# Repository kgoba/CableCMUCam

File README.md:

Automatic motion tracking with CMUCam Pixy camera and CableCam, implemented on MBED Nucleo board.

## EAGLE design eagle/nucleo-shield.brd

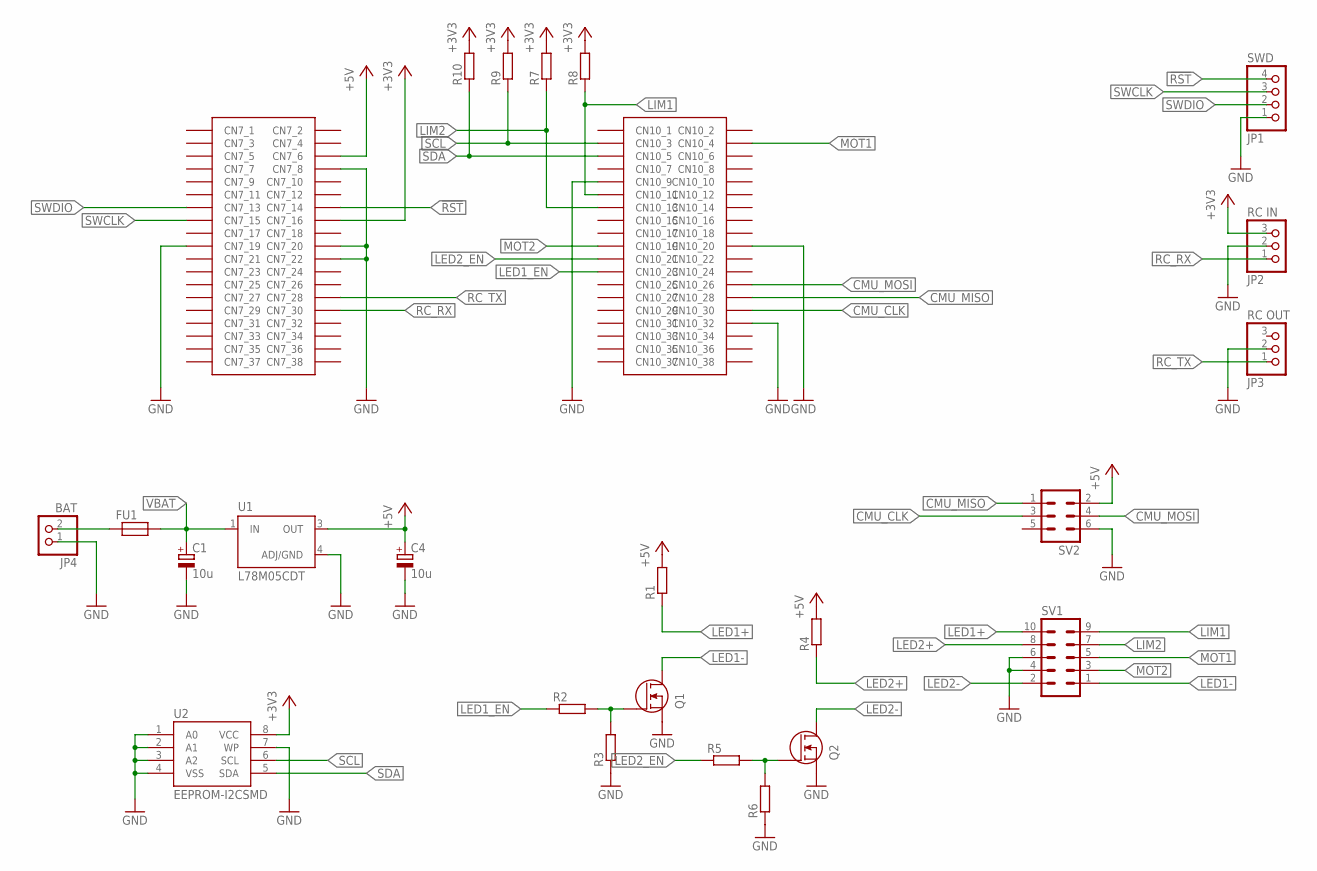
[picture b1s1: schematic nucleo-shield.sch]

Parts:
C1, C4: 10u; SMC_A
FU1: PTC_FUSE; C1812K
JP1: SWD; 1X04
JP2: RC IN; 1X03
JP3: RC OUT; 1X03
JP4: BAT; 1X02
Q1, Q2: MOSFET-N-SOT23-3; SOT23-3
R1, R2, R3, R4, R5, R6, R7, R8, R9, R10: R-EU_R0805; R0805
SV1: ML10L
SV2: ML6L
U1: L78M05CDT; DPAK
U2: EEPROM-I2CSMD; SO08
U$2: NUCLEO-MORPHO-64; NUCLEO-64-MORPHO

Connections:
!RST: JP1.4, U$2.CN7_14
+3V3: JP2.3, R7.2, R8.2, R9.2, R10.2, U2.8 (VCC), U$2.CN7_16
+5V: C4.+, R1.2, R4.2, SV2.2, U1.3 (OUT), U$2.CN7_6
CMU_CLK: SV2.3, U$2.CN10_30
CMU_MISO: SV2.1, U$2.CN10_28
CMU_MOSI: SV2.4, U$2.CN10_26
GND: C1.-, C4.-, JP1.1, JP2.2, JP3.2, JP4.1, Q1.2 (S), Q2.2 (S), R3.1, R6.1, SV1.4, SV1.6, SV2.6, U1.4 (ADJ/GND), U2.1 (A0), U2.2 (A1), U2.3 (A2), U2.4 (VSS), U2.7 (WP), U$2.CN7_8, U$2.CN7_19, U$2.CN7_20, U$2.CN7_22, U$2.CN10_9, U$2.CN10_20, U$2.CN10_32
LED1+: R1.1, SV1.10
LED1-: Q1.3 (D), SV1.1
LED1_EN: R2.1, U$2.CN10_23
LED2+: R4.1, SV1.8
LED2-: Q2.3 (D), SV1.2
LED2_EN: R5.1, U$2.CN10_21
LIM1: R8.1, SV1.9, U$2.CN10_11
LIM2: R7.1, SV1.7, U$2.CN10_13
MOT1: SV1.5, U$2.CN10_4
MOT2: SV1.3, U$2.CN10_19
unnamed: Q1.1 (G), R2.2, R3.2
unnamed: FU1.1, JP4.2
unnamed: Q2.1 (G), R5.2, R6.2
RC_RX: JP2.1, U$2.CN7_30
RC_TX: JP3.1, U$2.CN7_28
SCL: R9.1, U2.6 (SCL), U$2.CN10_3
SDA: R10.1, U2.5 (SDA), U$2.CN10_5
SWCLK: JP1.3, U$2.CN7_15
SWDIO: JP1.2, U$2.CN7_13
VBAT: C1.+, FU1.2, U1.1 (IN)

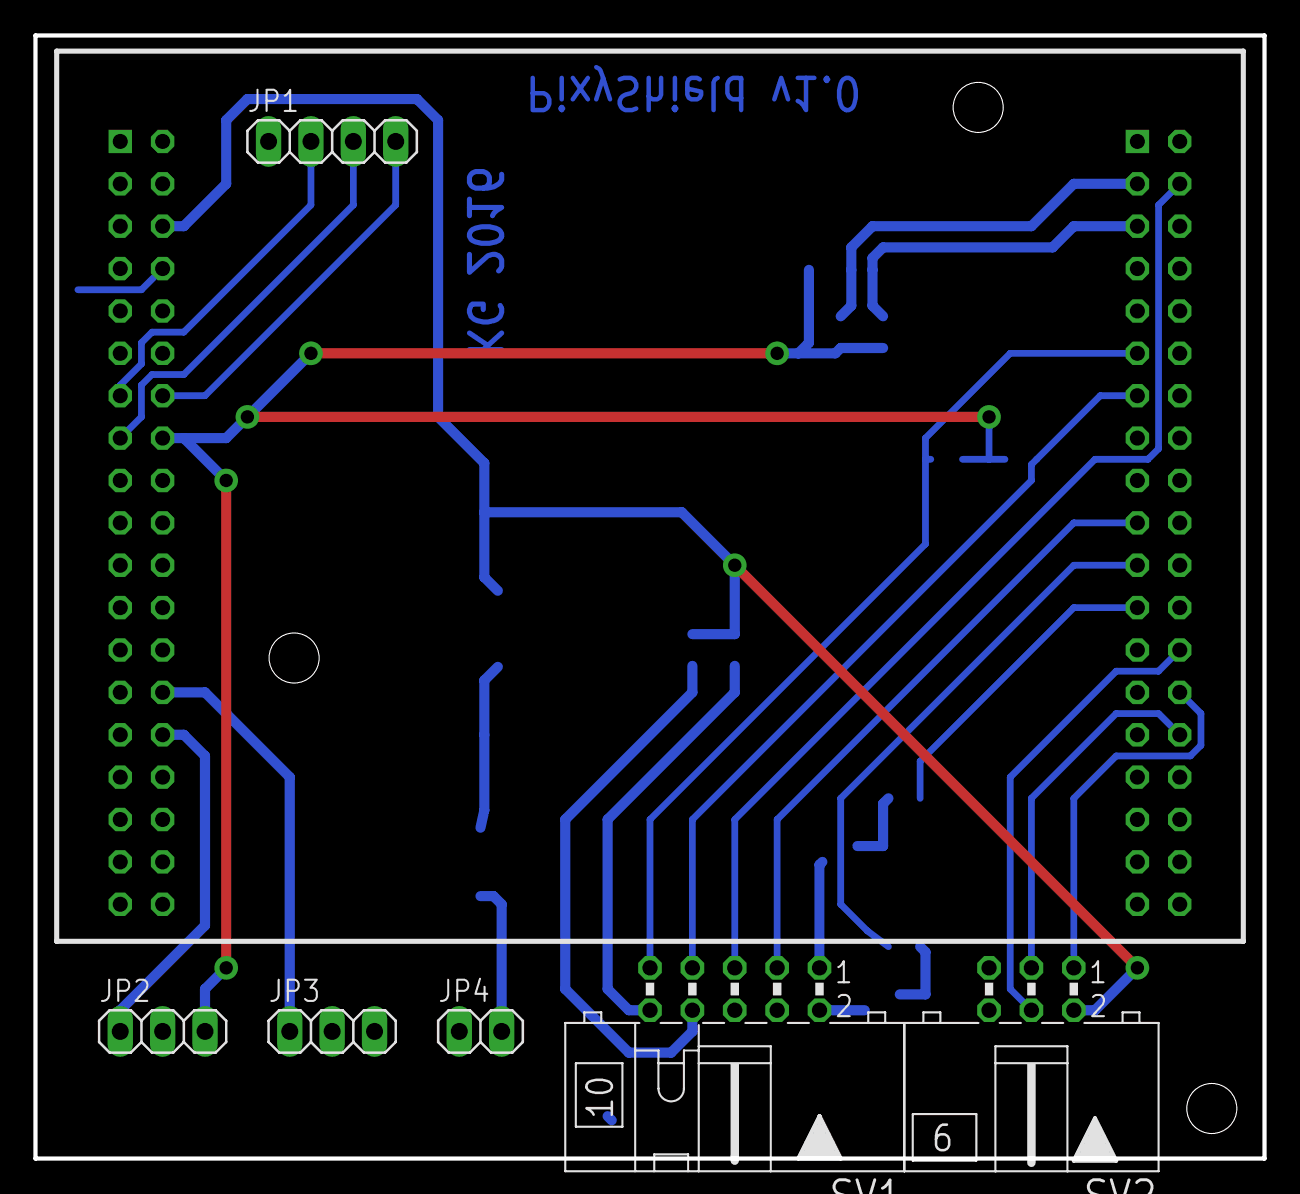
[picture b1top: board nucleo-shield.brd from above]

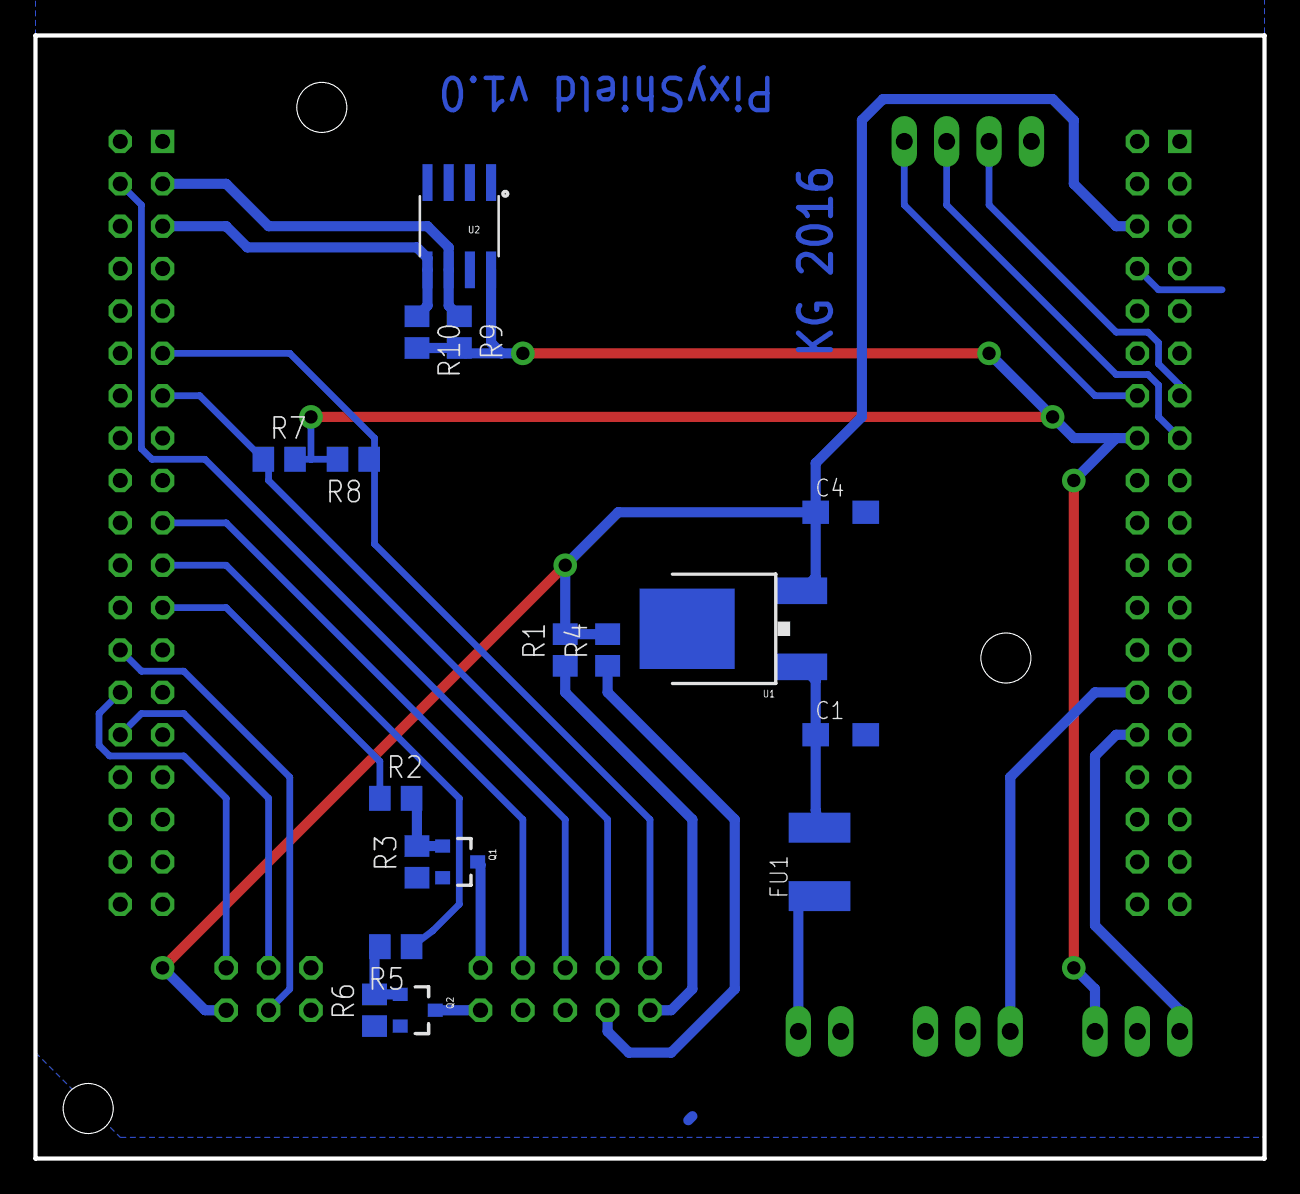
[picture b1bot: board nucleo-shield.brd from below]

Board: 2 copper layers, 73.7 x 67.3 mm, 24 parts (17 on the bottom side), 27 nets.

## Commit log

2016-10-27 Added source and schematic files
2016-10-28 Updated motor channels
2016-10-28 Added README
2016-11-01 Added cable manual control
2016-11-01 Added mbed settings

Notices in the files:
parts and their libraries:
SparkFun-DigitalIC: Licensing: Creative Commons ShareAlike 4.0 International - https://creativecommons.org/licenses/by-sa/4.0
